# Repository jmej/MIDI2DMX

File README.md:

# MIDI2DMX

## Teensy driven DJ light and LED control via MIDI

### This project was developed to facilitate curriculum at Portland Community College for the Music and Sonic Arts department

MIDI2DMX provides a simple way to get total control over a wide variety of lights - using existing music software (Ableton Live, Logic, Bitwig, Garage Band, Pro Tools etc), as well as hardware midi sequencers like the Akai MPC series, the Elektron Octatrack, Alesis MMT-8, etc. It allows for easy interfacing with programming environments like Pure Data, MaxMSP, and Processing.

This makes it easy to sequence lights for live music performances, do algorithmic light programming, map lights using sound analysis, data from the internet, or sensor data etc.

It unlocks cheap DJ lights turning them into flexible and expressive tools/instruments.

I designed a PCB to make the circuit easy to build, and have assembled quite a number of them with students in my interactivity courses at Portland Community College. There is no wiring, it's a quick project and costs around $40 total.

Eagle files for the PCB are published here - but you can also order them (in multiples of 3) from OSHPark: https://oshpark.com/shared_projects/hyqqaC5r

This core of the design is a Teensy - with some solid and extremely fast DMX code from Paul Stoffregen. The result is much smoother and more reliable than any commercial solution I've used. Because of Paul's usb drivers - it can be programmed to be a USB midi device, so it will show up in any MIDI capable software on any OS. The code in this repo is setup to translate midi cc's into DMX channel values. (Mapping CC numbers directly to DMX channel numbers).

We've used the Teensy 3.2 for our builds - but an LC should also work https://www.pjrc.com/store/teensy32.html

The additional parts are available from mouser here: http://www.mouser.com/ProjectManager/ProjectDetail.aspx?AccessID=11855f0a7f

If you want a more detailed guide I've published this: http://www.instructables.com/id/MIDI2DMX/

###Other DMX solutions
It turns out that it's pretty hard to find a good, well supported, inexpensive DMX controller.

There are a lot of expensive DMX controllers with proprietary drivers. There are a lot of cheap DMX controllers with little or no documentation. (Although these days a lot of them are copied from the uDMX project). Some of them work intermittently, some work only on windows, and some work only with specific (unexciting) DMX control software.

The uDMX project http://www.anyma.ch/research/udmx/ is the only well documented open source option out there, but in my experience - it's not that good. It suffers from choppy framerates and frequent drop outs, and on top of that, all the units I tried became unresponsive fairly often in a variety of software applications. There is a fundamental design flaw: it relies on your computer to send DMX frames. If your computer is processing audio (from Pure Data or Max for instance) - you end up with pretty severe audio dropouts. Also your framerate suffers due to various computer and USB bus performance issues. By contrast - this code makes the Teensy handle sending all the DMX frames, it just keeps the current channel values in an array that gets updated as midi data gets sent. So only value changes get transmitted via USB and the Teensy does the work of sending continual, fast frames whether they get updated or not. There is no pause in the Arduino loop - it sends out frames as fast as it can resulting in super smooth curves and animations.

##PD:
In the PD folder you'll find a few example patches for Pure Data (http://puredata.info/). While you can control lights using this board from anything that can send midi - PD offers a lot more options and flexibility than most other midi software. I run patches like these on a Raspberry Pi for live use.

DMX_color_presets.pd shows how to translate RGB and HSV color values into messages you can send to your lights. Google has a nice color picker tool. https://www.google.com/webhp?sourceid=chrome-instant&ion=1&espv=2&ie=UTF-8#q=color%20picker

hsv2rbg.pd is an abstraction that the other patches rely on. All of these pd patches need to be put in the same folder to work correctly.

DMX_color_organ.pd has a simple midi mapping using Scriabin's pitch-color associations. https://en.wikipedia.org/wiki/Clavier_%C3%A0_lumi%C3%A8res

This makes any DMX light playable from a midi keyboard or midi sequencer like Ableton Live, Logic, Bitwig - as well as hardware sequencers like MPCs and Octatracks. This is my preferred method for programming custom light shows for live PA's.

Finally DMX_audio_analysis.pd demonstrates pitch and amplitude tracking and translation into light color and intensity using pd.

##Hardware Midi:
The hardware midi part of this board is untested - and the code doesn't support it yet. But it probably works, it just needs some arduino code to handle midi input on the Teensy's second Serial RX line.

##Future Dev:
Aside from implementing hardware midi - the plan is to setup some color and envelope control on the Teensy to replace some of work I'm currently doing with PD. An enclosure is also in progress.

##Schematic Errata:
Even though the schematic shows a PC110 optocoupler - it is actually wired and laid out for a Sharp PC900V optocoupler. The schmetic is correct - as long as you use a PC900V and not a PC110. It would need to be changed for a different optocoupler.

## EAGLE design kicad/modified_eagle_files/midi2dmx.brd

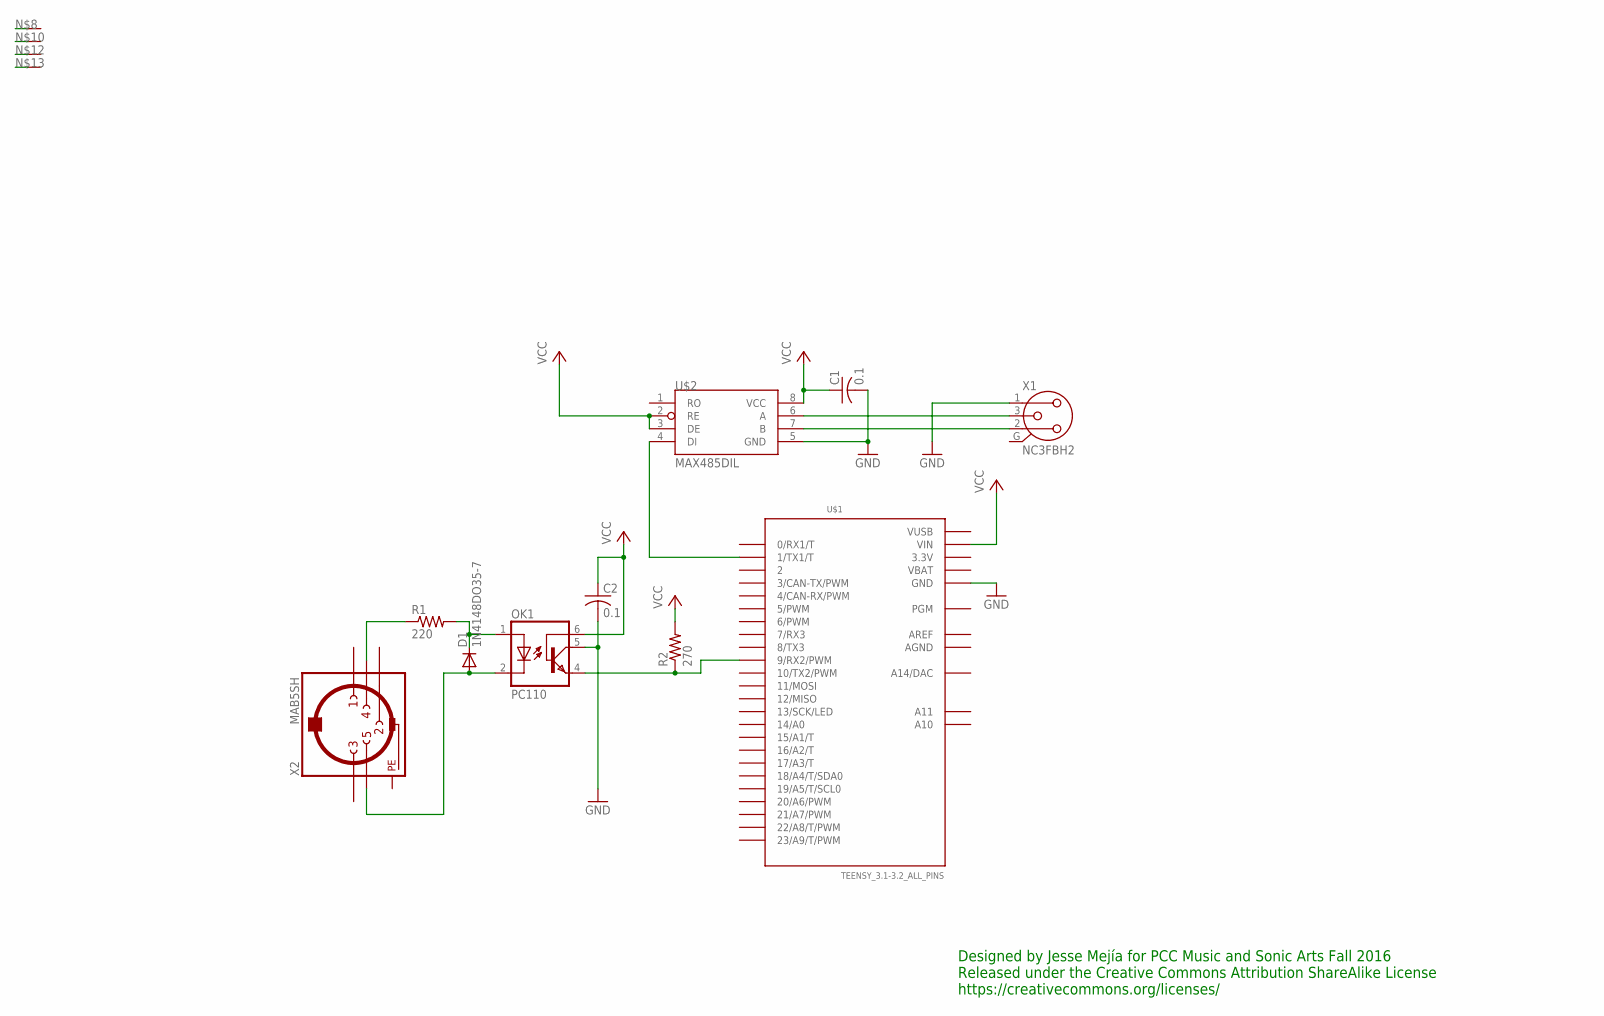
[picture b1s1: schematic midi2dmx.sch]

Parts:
C1, C2: 0.1; C025-024X044
D1: 1N4148DO35-7; DO35-7
OK1: PC110; DIL06
R1: 220; 0309/12
R2: 270; 0309/12
U$1: TEENSY_3.1-3.2_ALL_PINS; TEENSY_3.0-3.2&LC_ALL_PINS
U$2: MAX485DIL; DIL08
VP_0, VP_1, VP_2, VP_3: VPDEV0; VPAC0
X1: NC3FBH2
X2: MAB5SH

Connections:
3.3V: U$1.3.3V, U$1.3.3V1 (3.3V)
AGND: U$1.AGND
AREF: U$1.AREF
GND: C1.2, C2.2, OK1.5 (COL), U$1.GND, U$1.GND1 (GND), U$2.5 (GND), X1.1
unnamed: U$1.1 (1/TX1/T), U$2.4 (DI)
unnamed: U$2.6 (A), X1.3
unnamed: U$2.7 (B), X1.2
unnamed: D1.C, OK1.1 (A), R1.2
unnamed: OK1.4 (EMI), R2.1, U$1.9 (9/RX2/PWM)
unnamed: R1.1, X2.4
unnamed: D1.A, OK1.2 (C), X2.5
PE: X2.PE, X2.PE@ (PE)
VBAT: U$1.VBAT
VCC: C1.1, C2.1, OK1.6 (BAS), R2.2, U$1.VIN, U$2.2 (RE), U$2.3 (DE), U$2.8 (VCC)
VUSB: U$1.VUSB

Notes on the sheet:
Designed by Jesse Mejía for PCC Music and Sonic Arts Fall 2016 Released under the Creative Commons Attribution ShareAlike License https://creativecommons.org/licenses/

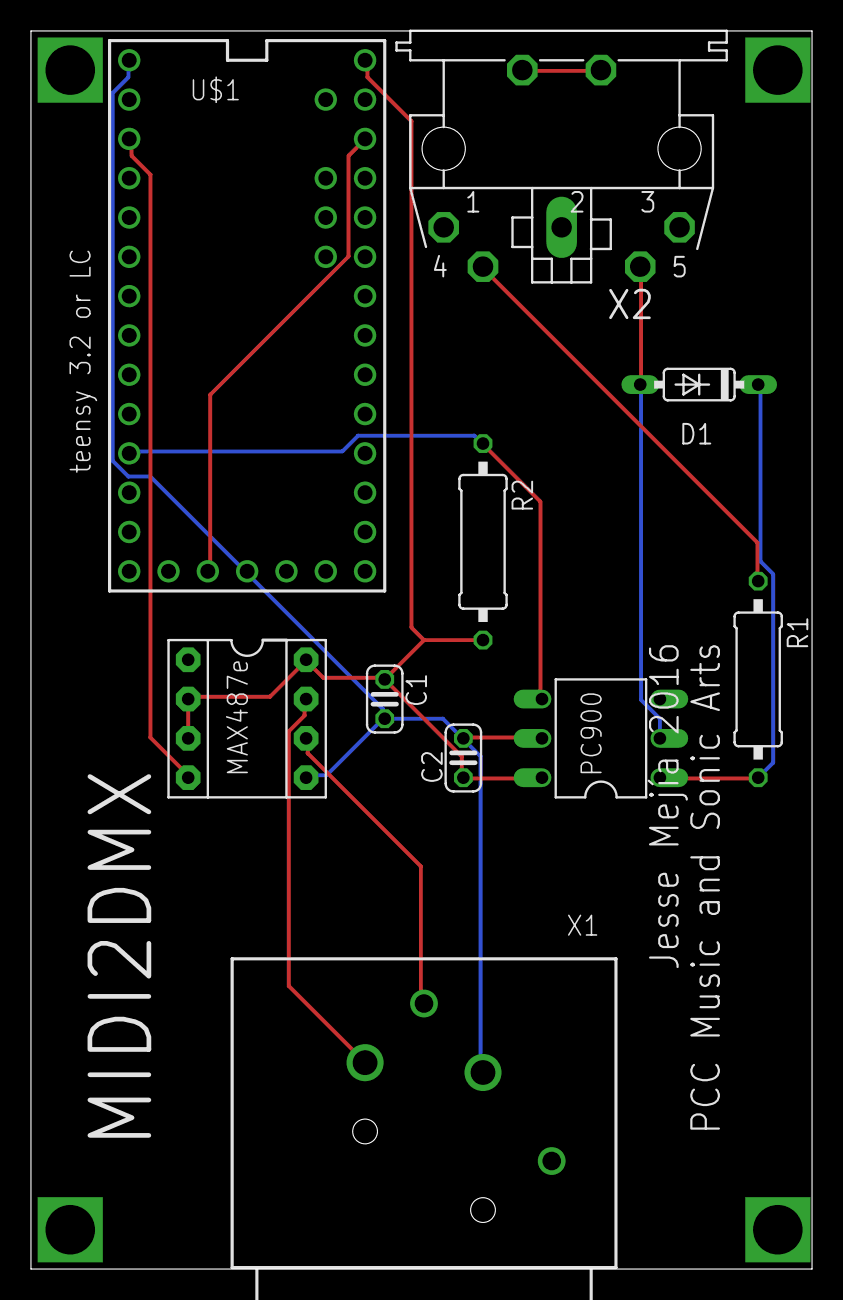
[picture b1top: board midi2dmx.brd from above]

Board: 2 copper layers, 50.5 x 80.0 mm, 14 parts (0 on the bottom side), 11 nets.

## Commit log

2016-11-27 Minor fix in DMX code, only needed for larger # of DMX channels
2017-09-05 adds simple standalone demo
2018-06-30 untested midi note funcionality
2019-03-12 initial conversion to kicad
2019-03-12 rev2 schematic work
2019-03-20 remove tiny labels
2019-06-12 adds support for 512 dmx channels
2019-06-12 Revert "adds support for 512 dmx channels"
    This reverts commit ce72b4abcd339d6fd9302ca5fe8feac92f709eb6.
2019-10-16 removing test file
2019-10-16 adds back channel expansion
2019-10-16 wip for note mode
2019-12-21 adds lasercut case plans in progress, removes broken NoteIn stuff
2020-01-15 fixes channel update again
2020-01-22 some board work and variable name change
2020-01-29 updates schematic for v2
2020-02-17 rev2 pcb almost ready for fab
2022-05-20 Change the device name to 'MIDI2DMX'
    Added names.c file to change the name that identifies the device in the OS
2022-12-06 changes example from RGBW to RGB
2022-12-06 cleanup of fade example
2023-03-02 swapped teensy with rp2030
2023-03-02 schematic in progress for 2040
2024-05-18 adds max example
2025-02-12 adds color organ example
2025-03-05 rp2040 port and new pcb rev wip
2025-03-17 dmx implementation working, colors and timing wip
2025-03-17 fixes color bug that was disguised as a timing bug
2025-03-17 started pcb based on the rp2040 dev board
2025-03-18 working
2025-03-18 pcb wip
2025-04-01 channelized color organ
2026-04-29 kicad wip

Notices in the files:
parts and their libraries:
SparkFun-DigitalIC: Licensing: Creative Commons ShareAlike 4.0 International - https://creativecommons.org/licenses/by-sa/4.0
